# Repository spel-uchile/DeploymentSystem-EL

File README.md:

# DeploymentSystem-EL
Proyecto de curso EL. Diseño de sistema de despliegue

#### Parte eléctrica
 - Diseñar una nueva placa con un micro más pequeño y utilizando el espacio en los InterStage.
 - Revisar documentacion de Pinout de Stack (https://docs.google.com/spreadsheets/d/16q0HoTVAfZYG_5lE80G09ZOd-HxBMbC0y2KJIxqkWWU/edit#gid=0).
 - Instrucciones con comandos. 
 
#### Parte Mecánica
 - Revisar articulaciones en CAD (Carpeta general de CAD: https://drive.google.com/drive/u/0/folders/1X1Ea6DyqA-4cPEp2hvyv38Jz5EprBwpk).
   "NO MODIFICAR DIRECTAMENTE"
 - Leer CubesatRev 13 especificaciones de diseños (Tolerancias de diseños, dimensiones maximas de extrucción, estandar de dimensión). https://www.cubesat.org/resources.
 - Exportar las caras de los InterStage a DXF para el diseño del Board.
 - Crear articulaciones en los paneles.

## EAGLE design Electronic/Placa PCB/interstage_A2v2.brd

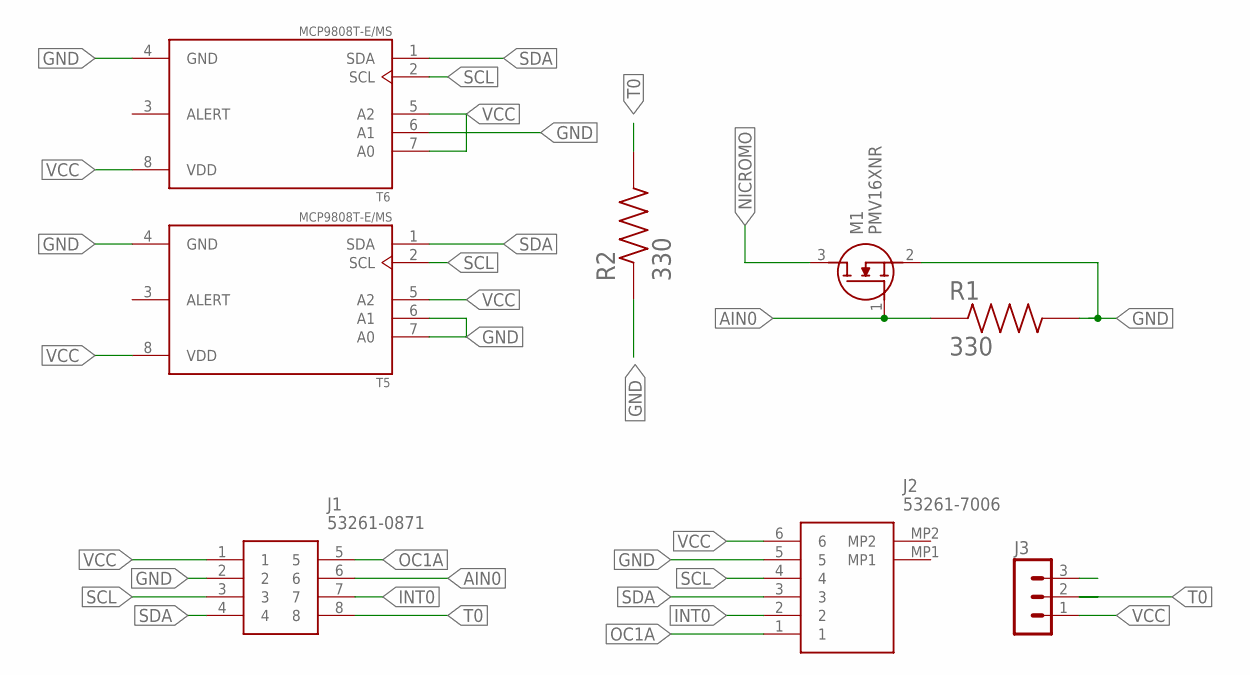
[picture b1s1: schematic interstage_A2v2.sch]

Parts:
J1: 53261-0871
J2: 53261-7006; 532617006
J3: MA03-1
M1: PMV16XNR; SOT95P230X110-3N
R1, R2: 330; RESC3216X70N
T5, T6: MCP9808T-E/MS; SOP65P490X110-8N

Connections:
AIN0: J1.6, M1.1 (G), R1.1
GND: J1.2, J2.5, M1.2 (S), R1.2, R2.1, T5.4 (GND), T5.6 (A1), T5.7 (A0), T6.4 (GND), T6.6 (A1)
INT0: J1.7, J2.2
NICROMO: M1.3 (D)
OC1A: J1.5, J2.1
SCL: J1.3, J2.4, T5.2 (SCL), T6.2 (SCL)
SDA: J1.4, J2.3, T5.1 (SDA), T6.1 (SDA)
T0: J1.8, J3.2, R2.2
VCC: J1.1, J2.6, J3.1, T5.5 (A2), T5.8 (VDD), T6.5 (A2), T6.7 (A0), T6.8 (VDD)

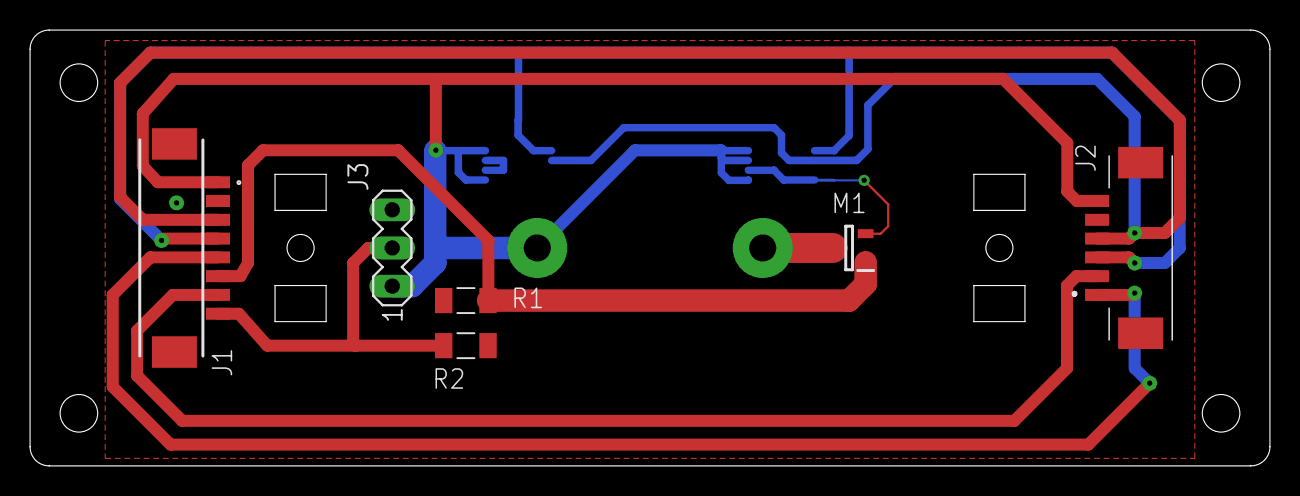
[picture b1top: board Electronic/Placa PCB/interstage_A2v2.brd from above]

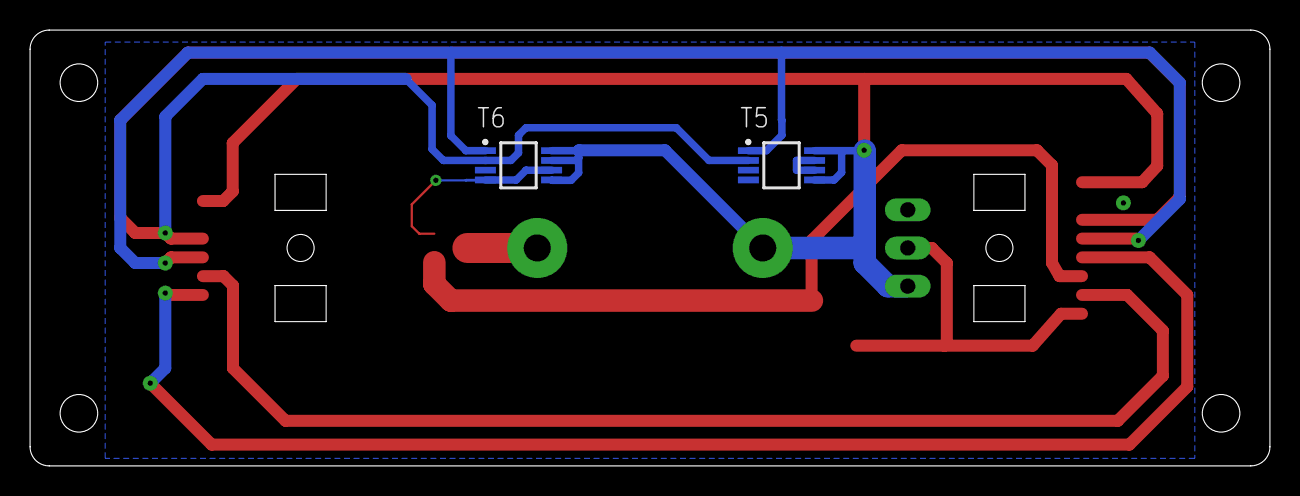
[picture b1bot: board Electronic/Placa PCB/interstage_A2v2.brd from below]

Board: 2 copper layers, 82.5 x 29.0 mm, 8 parts (2 on the bottom side), 8 nets.

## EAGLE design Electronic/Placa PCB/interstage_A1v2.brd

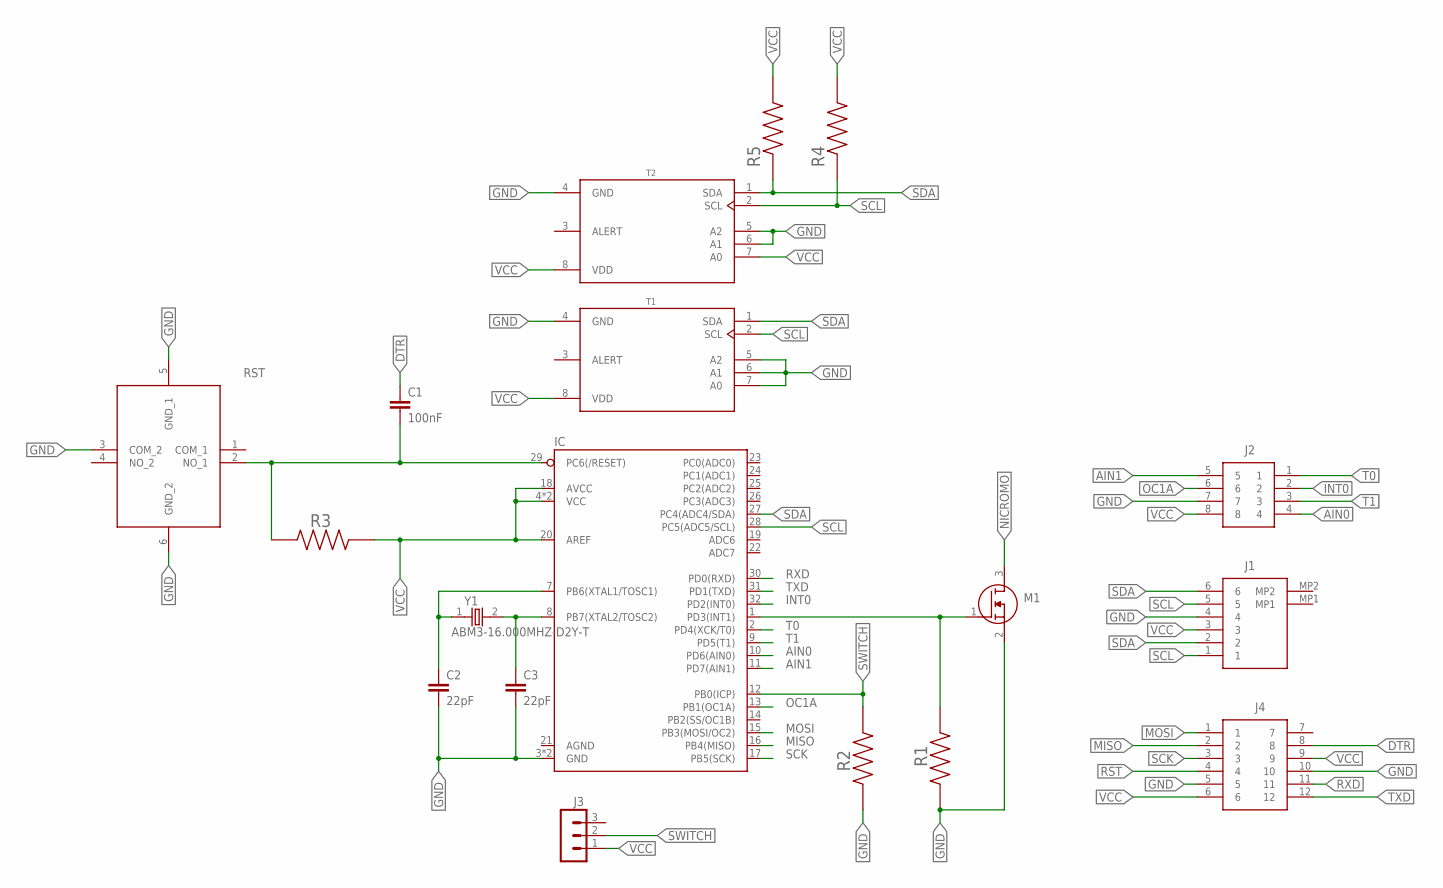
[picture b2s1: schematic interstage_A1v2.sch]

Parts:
C1: 100nF; C0805K
C2, C3: 22pF; C0603K
IC: ATMEGA328P_TQFP; TQFP32-08
J1: 53261-7006; 532617006
J2: 53261-0871
J3: MA03-1
J4: 53261-1271
M1: PMV16XNR; SOT95P230X110-3N
R1, R2: 330; RESC3216X70N
R3: 10k; RESC3216X70N
R4, R5: 4.7k; RESC3216X70N
RST: 431151015826
T1, T2: MCP9808T-E/MS; SOP65P490X110-8N
Y1: ABM3-16.000MHZ-D2Y-T; XTAL500X320X130N

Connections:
AIN0: IC.10 (PD6(AIN0)), J2.4
AIN1: IC.11 (PD7(AIN1)), J2.5
DTR: C1.1, J4.8
GND: C2.2, C3.2, IC.3 (GND), IC.5 (GND), J1.4, J2.7, J4.5, J4.10, M1.2 (S), R1.2, R2.1, RST.3 (COM_2), RST.5 (GND_1), RST.6 (GND_2), T1.4 (GND), T1.5 (A2), T1.6 (A1), T1.7 (A0), T2.4 (GND), T2.5 (A2), T2.6 (A1)
INT0: IC.32 (PD2(INT0)), J2.2
INT1: IC.1 (PD3(INT1)), M1.1 (G), R1.1
MISO: IC.16 (PB4(MISO)), J4.2
MOSI: IC.15 (PB3(MOSI/OC2)), J4.1
unnamed: C2.1, IC.7 (PB6(XTAL1/TOSC1)), Y1.1
unnamed: C3.1, IC.8 (PB7(XTAL2/TOSC2)), Y1.2
NICROMO: M1.3 (D)
OC1A: IC.13 (PB1(OC1A)), J2.6
RST: C1.2, IC.29 (PC6(/RESET)), J4.4, R3.1, RST.2 (NO_1)
RXD: IC.30 (PD0(RXD)), J4.11
SCK: IC.17 (PB5(SCK)), J4.3
SCL: IC.28 (PC5(ADC5/SCL)), J1.1, J1.5, R4.1, T1.2 (SCL), T2.2 (SCL)
SDA: IC.27 (PC4(ADC4/SDA)), J1.2, J1.6, R5.1, T1.1 (SDA), T2.1 (SDA)
SWITCH: IC.12 (PB0(ICP)), J3.2, R2.2
T0: IC.2 (PD4(XCK/T0)), J2.1
T1: IC.9 (PD5(T1)), J2.3
TXD: IC.31 (PD1(TXD)), J4.12
VCC: IC.4 (VCC), IC.6 (VCC), IC.18 (AVCC), IC.20 (AREF), J1.3, J2.8, J3.1, J4.6, J4.9, R3.2, R4.2, R5.2, T1.8 (VDD), T2.7 (A0), T2.8 (VDD)

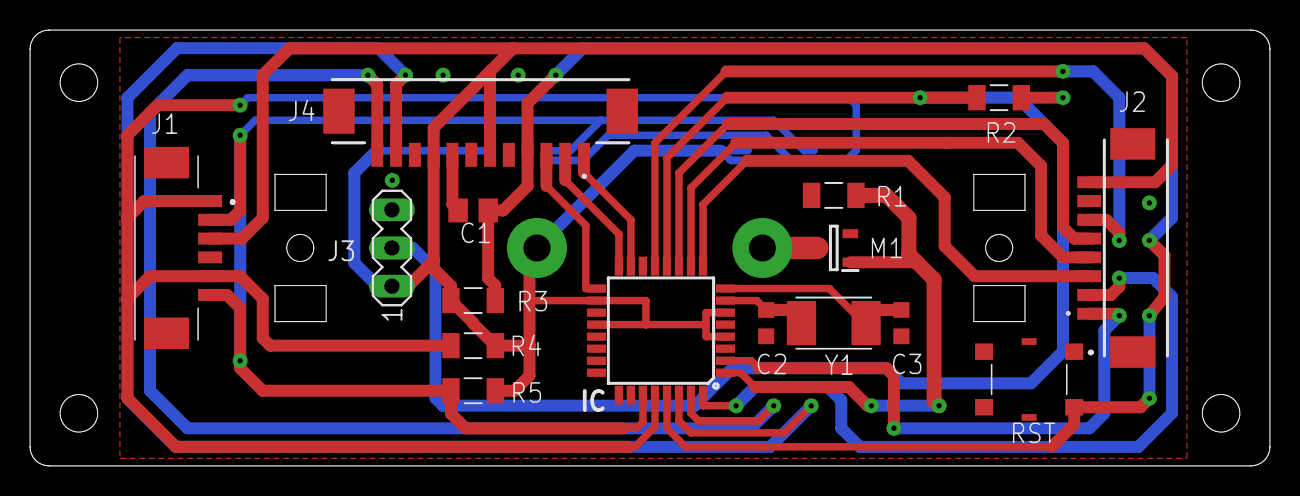
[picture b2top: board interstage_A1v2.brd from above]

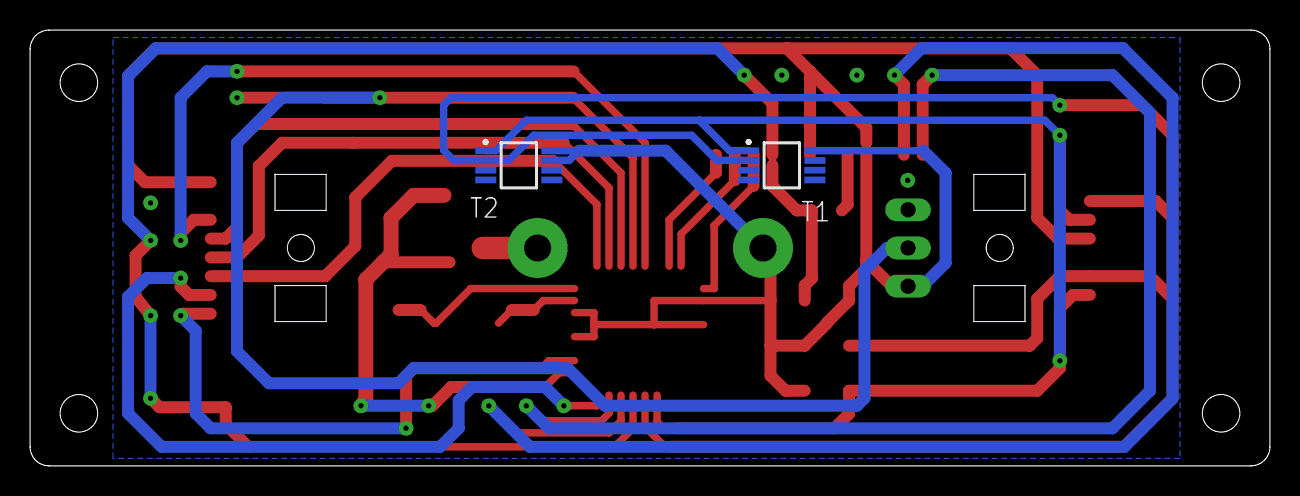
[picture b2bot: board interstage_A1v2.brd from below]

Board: 2 copper layers, 82.5 x 29.0 mm, 18 parts (2 on the bottom side), 21 nets.

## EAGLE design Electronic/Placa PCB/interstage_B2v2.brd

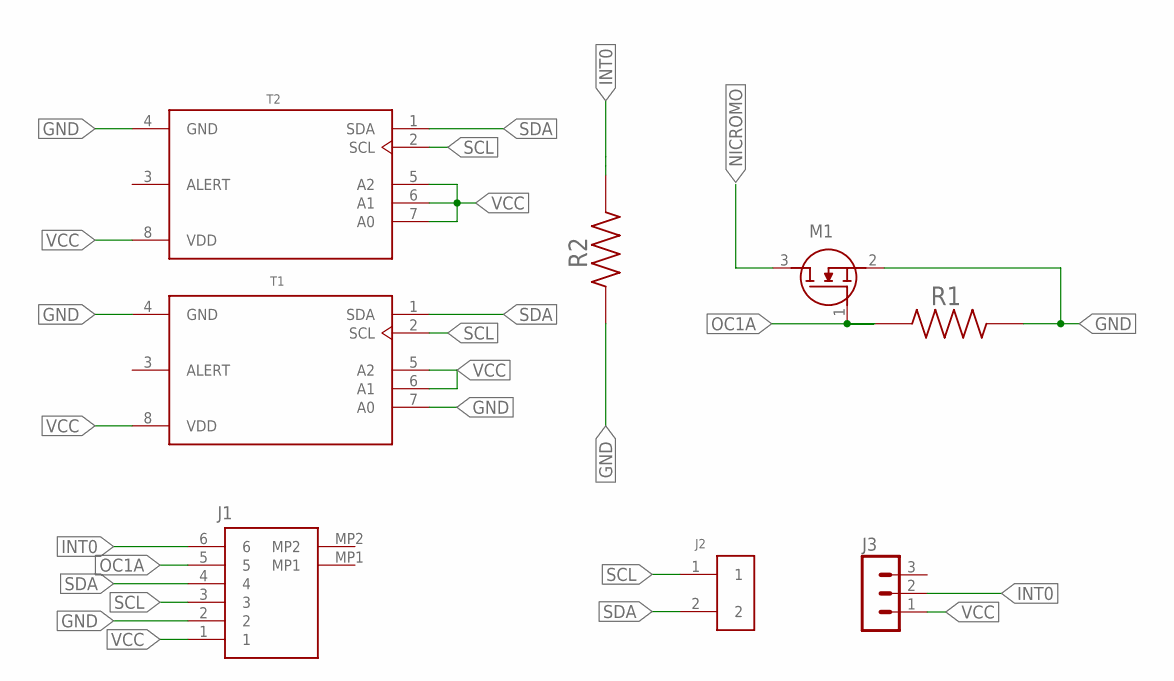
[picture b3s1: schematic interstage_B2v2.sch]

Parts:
J1: 53261-7006; 532617006
J2: 0532610271; MOLEX_0532610271
J3: MA03-1
M1: PMV16XNR; SOT95P230X110-3N
R1, R2: 330; RESC3216X70N
T1, T2: MCP9808T-E/MS; SOP65P490X110-8N

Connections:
GND: J1.2, M1.2 (S), R1.2, R2.1, T1.4 (GND), T1.7 (A0), T2.4 (GND)
INT0: J1.6, J3.2, R2.2
NICROMO: M1.3 (D)
OC1A: J1.5, M1.1 (G), R1.1
SCL: J1.3, J2.1, T1.2 (SCL), T2.2 (SCL)
SDA: J1.4, J2.2, T1.1 (SDA), T2.1 (SDA)
VCC: J1.1, J3.1, T1.5 (A2), T1.6 (A1), T1.8 (VDD), T2.5 (A2), T2.6 (A1), T2.7 (A0), T2.8 (VDD)

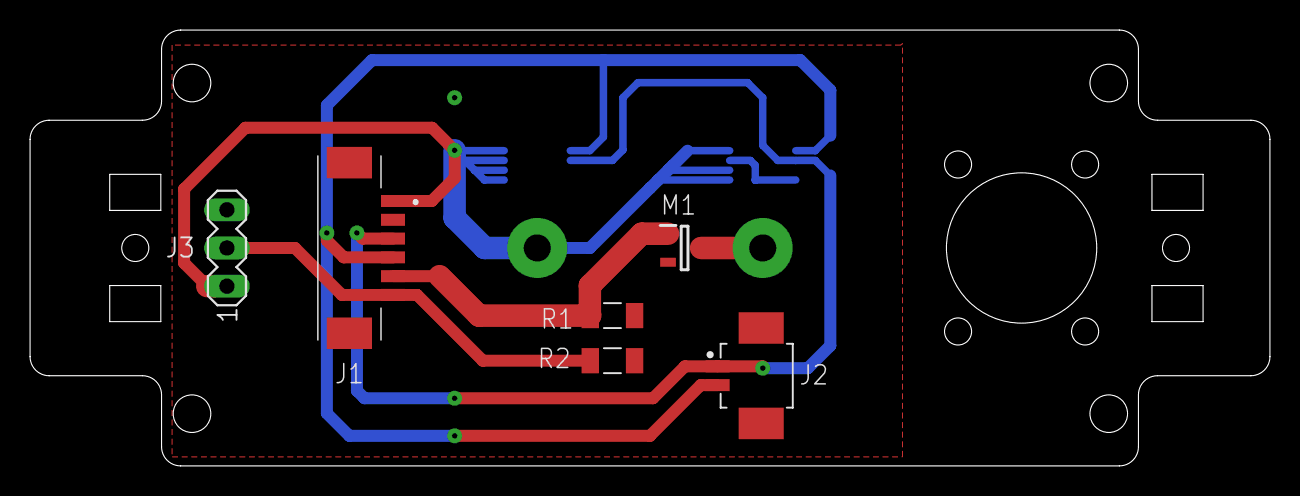
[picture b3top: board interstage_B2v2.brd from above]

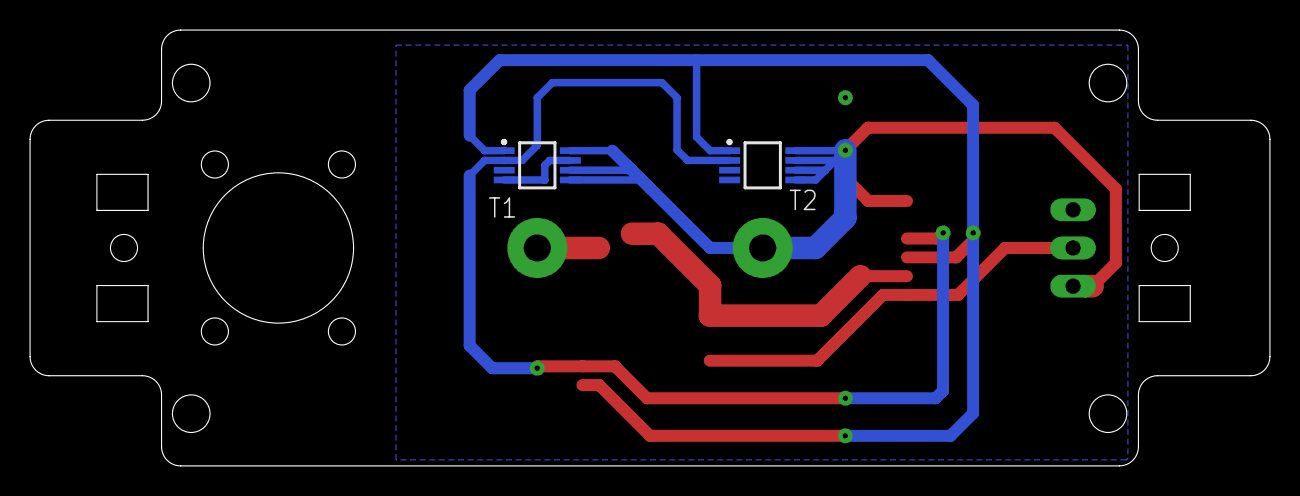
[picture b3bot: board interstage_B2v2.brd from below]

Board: 2 copper layers, 82.5 x 29.0 mm, 8 parts (2 on the bottom side), 6 nets.

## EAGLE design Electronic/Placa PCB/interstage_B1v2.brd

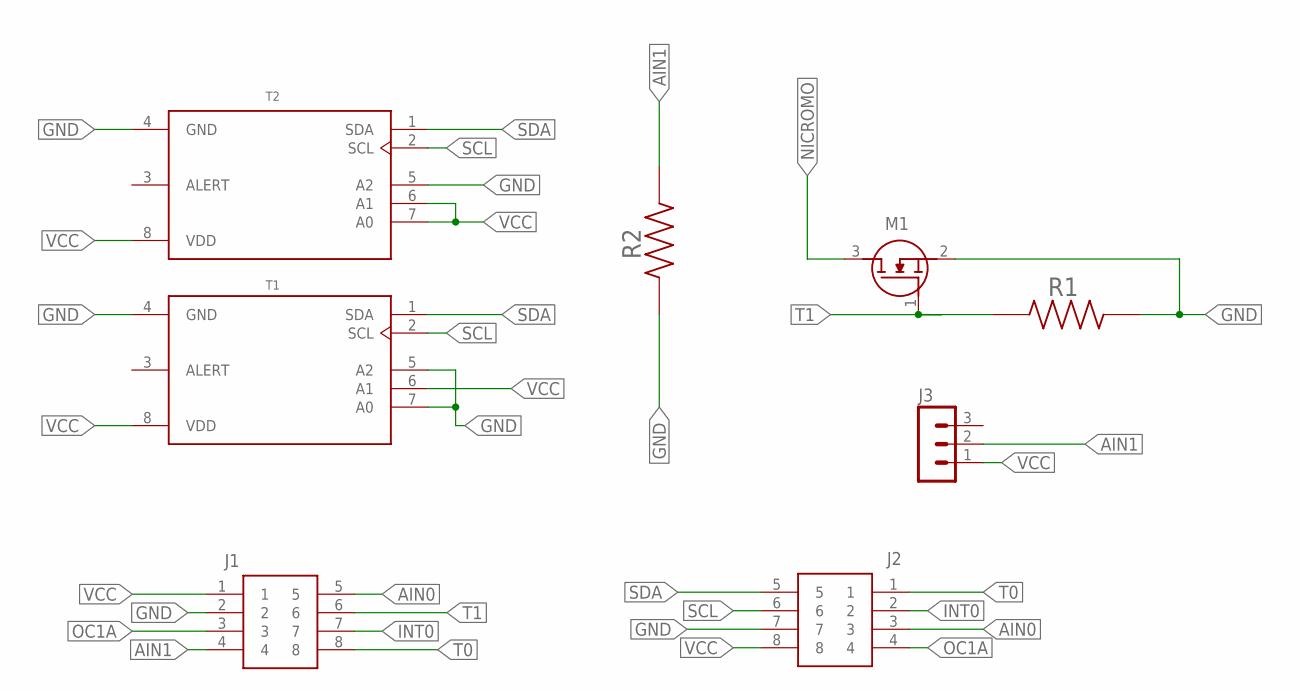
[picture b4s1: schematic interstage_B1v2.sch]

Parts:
J1, J2: 53261-0871
J3: MA03-1
M1: PMV16XNR; SOT95P230X110-3N
R1, R2: 330; RESC3216X70N
T1, T2: MCP9808T-E/MS; SOP65P490X110-8N

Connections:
AIN0: J1.5, J2.3
AIN1: J1.4, J3.2, R2.2
GND: J1.2, J2.7, M1.2 (S), R1.2, R2.1, T1.4 (GND), T1.5 (A2), T1.7 (A0), T2.4 (GND), T2.5 (A2)
INT0: J1.7, J2.2
NICROMO: M1.3 (D)
OC1A: J1.3, J2.4
SCL: J2.6, T1.2 (SCL), T2.2 (SCL)
SDA: J2.5, T1.1 (SDA), T2.1 (SDA)
T0: J1.8, J2.1
T1: J1.6, M1.1 (G), R1.1
VCC: J1.1, J2.8, J3.1, T1.6 (A1), T1.8 (VDD), T2.6 (A1), T2.7 (A0), T2.8 (VDD)

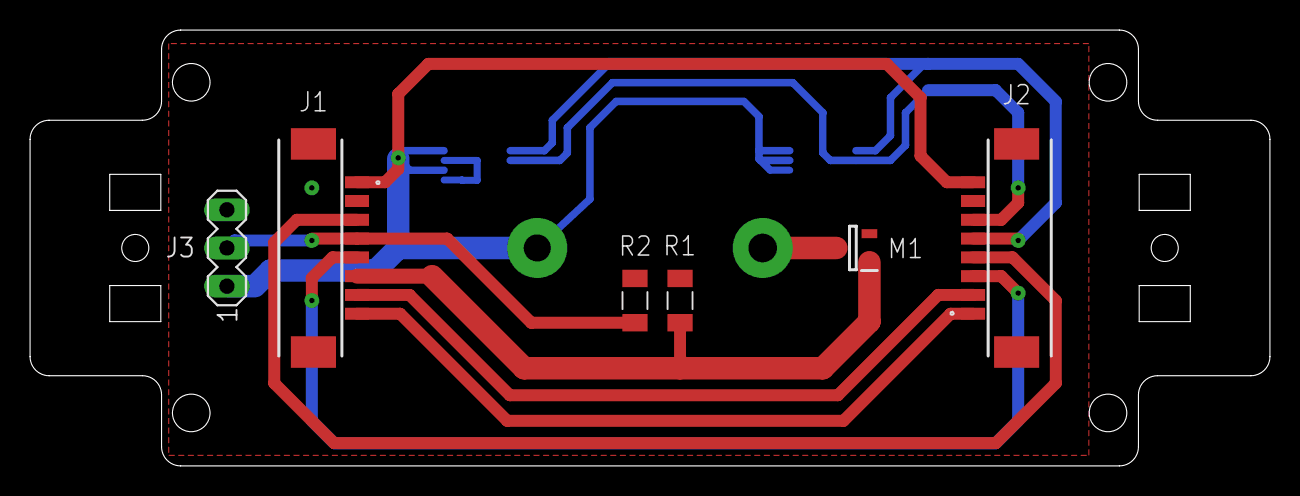
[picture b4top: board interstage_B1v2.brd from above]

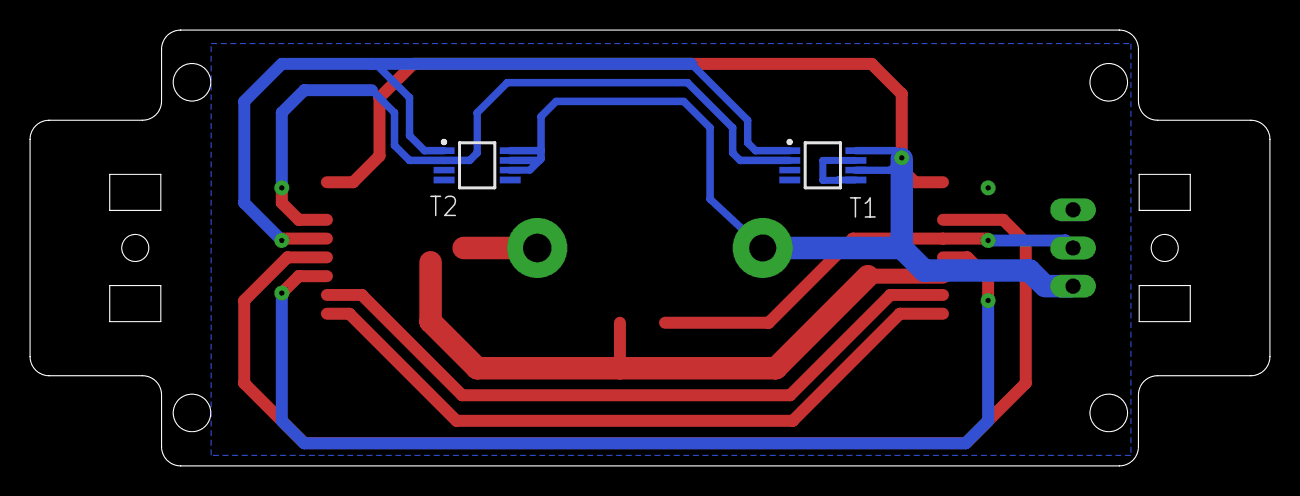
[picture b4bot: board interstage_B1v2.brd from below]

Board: 2 copper layers, 82.5 x 29.0 mm, 8 parts (2 on the bottom side), 10 nets.

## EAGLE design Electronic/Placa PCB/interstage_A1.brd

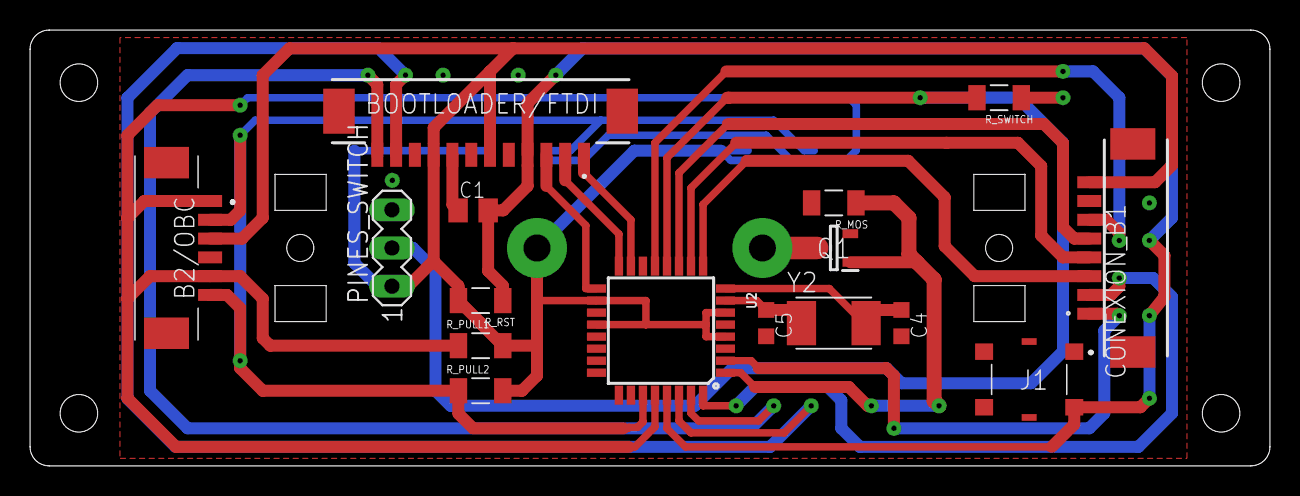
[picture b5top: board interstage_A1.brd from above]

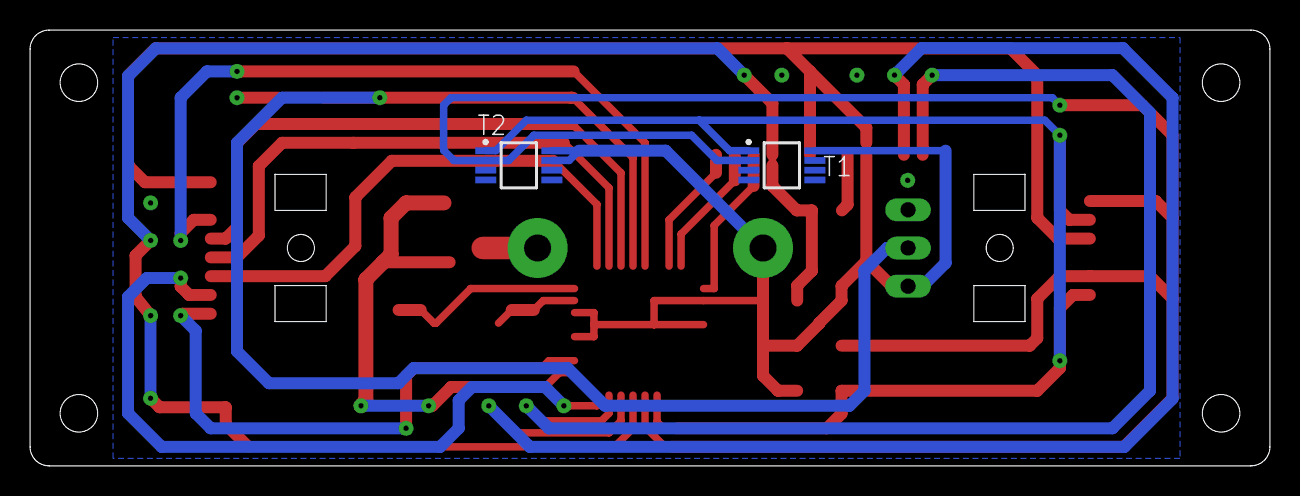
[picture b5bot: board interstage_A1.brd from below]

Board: 2 copper layers, 82.5 x 29.0 mm, 18 parts (2 on the bottom side), 21 nets.

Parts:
B2/OBC: 53261-7006; 532617006
BOOTLOADER/FTDI: 53261-1271
C1: 100nF; C0805K
C4, C5: 22pF; C0603K
CONEXION_B1: 53261-0871
J1: 431151015826
PINES_SWITCH: MA03-1
Q1: PMV16XNR; SOT95P230X110-3N
R_MOS: ERA-8AEB331V; RESC3216X70N
R_PULL1, R_PULL2: ERA-8AEB472V; RESC3216X70N
R_RST: ERA-8AEB103V; RESC3216X70N
R_SWITCH: ERA-8AEB331V; RESC3216X70N
T1, T2: MCP9808T-E/MS; SOP65P490X110-8N
U2: ATMEGA328P_TQFP; TQFP32-08
Y2: ABM3-16.000MHZ-D2Y-T; XTAL500X320X130N

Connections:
AIN0: CONEXION_B1.4, U2.10
AIN1: CONEXION_B1.5, U2.11
DTR: BOOTLOADER/FTDI.8, C1.1
GND: B2/OBC.4, BOOTLOADER/FTDI.5, BOOTLOADER/FTDI.10, C4.2, C5.2, CONEXION_B1.7, J1.3, J1.5, J1.6, Q1.2, R_MOS.2, R_SWITCH.1, T1.4, T1.5, T1.6, T1.7, T2.4, T2.5, T2.6, U2.3, U2.5
INT0: CONEXION_B1.2, U2.32
INT1: Q1.1, R_MOS.1, U2.1
MISO: BOOTLOADER/FTDI.2, U2.16
MOSI: BOOTLOADER/FTDI.1, U2.15
unnamed: C5.1, U2.7, Y2.1
unnamed: C4.1, U2.8, Y2.2
OC1A: CONEXION_B1.6, U2.13
RST: BOOTLOADER/FTDI.4, C1.2, J1.2, R_RST.1, U2.29
RXD: BOOTLOADER/FTDI.11, U2.30
SCK: BOOTLOADER/FTDI.3, U2.17
SCL: B2/OBC.1, B2/OBC.5, R_PULL1.1, T1.2, T2.2, U2.28
SDA: B2/OBC.2, B2/OBC.6, R_PULL2.1, T1.1, T2.1, U2.27
SWITCH: PINES_SWITCH.2, R_SWITCH.2, U2.12
T0: CONEXION_B1.1, U2.2
T1: CONEXION_B1.3, U2.9
TXD: BOOTLOADER/FTDI.12, U2.31
VCC: B2/OBC.3, BOOTLOADER/FTDI.6, BOOTLOADER/FTDI.9, CONEXION_B1.8, PINES_SWITCH.1, R_PULL1.2, R_PULL2.2, R_RST.2, T1.8, T2.7, T2.8, U2.4, U2.6, U2.18, U2.20

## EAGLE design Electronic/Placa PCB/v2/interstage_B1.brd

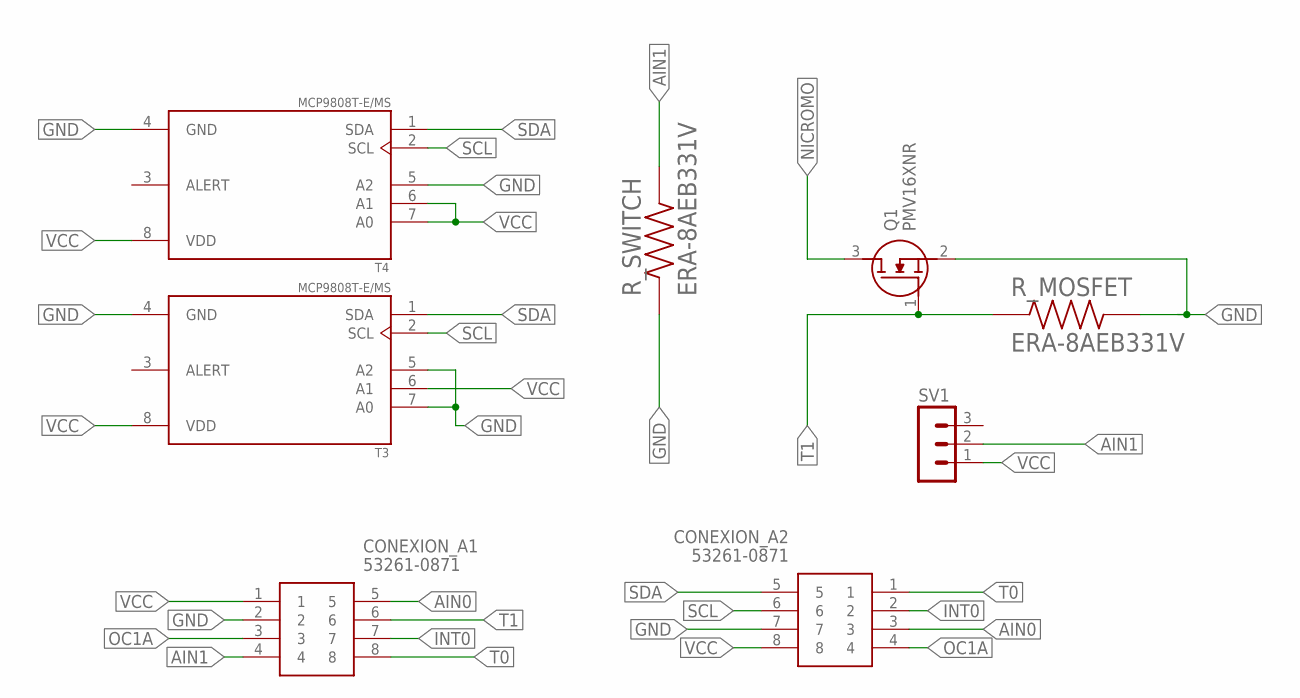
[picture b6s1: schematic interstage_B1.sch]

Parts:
CONEXION_A1, CONEXION_A2: 53261-0871
Q1: PMV16XNR; SOT95P230X110-3N
R_MOSFET: ERA-8AEB331V; RESC3216X70N
R_SWITCH: ERA-8AEB331V; RESC3216X70N
SV1: MA03-1
T3, T4: MCP9808T-E/MS; SOP65P490X110-8N

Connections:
AIN0: CONEXION_A1.5, CONEXION_A2.3
AIN1: CONEXION_A1.4, R_SWITCH.2, SV1.2
GND: CONEXION_A1.2, CONEXION_A2.7, Q1.2 (S), R_MOSFET.2, R_SWITCH.1, T3.4 (GND), T3.5 (A2), T3.7 (A0), T4.4 (GND), T4.5 (A2)
INT0: CONEXION_A1.7, CONEXION_A2.2
NICROMO: Q1.3 (D)
OC1A: CONEXION_A1.3, CONEXION_A2.4
SCL: CONEXION_A2.6, T3.2 (SCL), T4.2 (SCL)
SDA: CONEXION_A2.5, T3.1 (SDA), T4.1 (SDA)
T0: CONEXION_A1.8, CONEXION_A2.1
T1: CONEXION_A1.6, Q1.1 (G), R_MOSFET.1
VCC: CONEXION_A1.1, CONEXION_A2.8, SV1.1, T3.6 (A1), T3.8 (VDD), T4.6 (A1), T4.7 (A0), T4.8 (VDD)

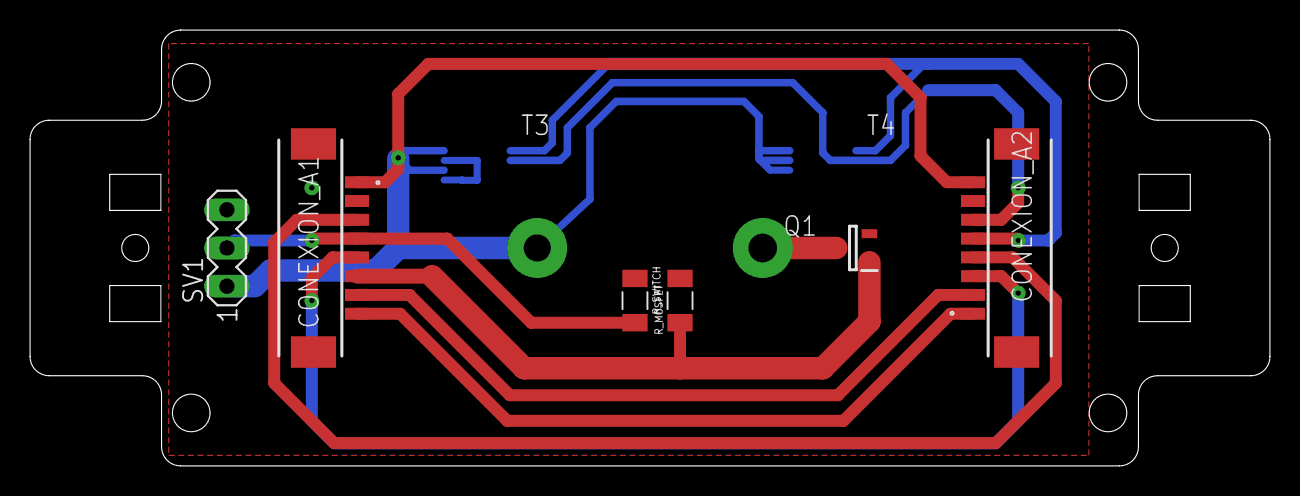
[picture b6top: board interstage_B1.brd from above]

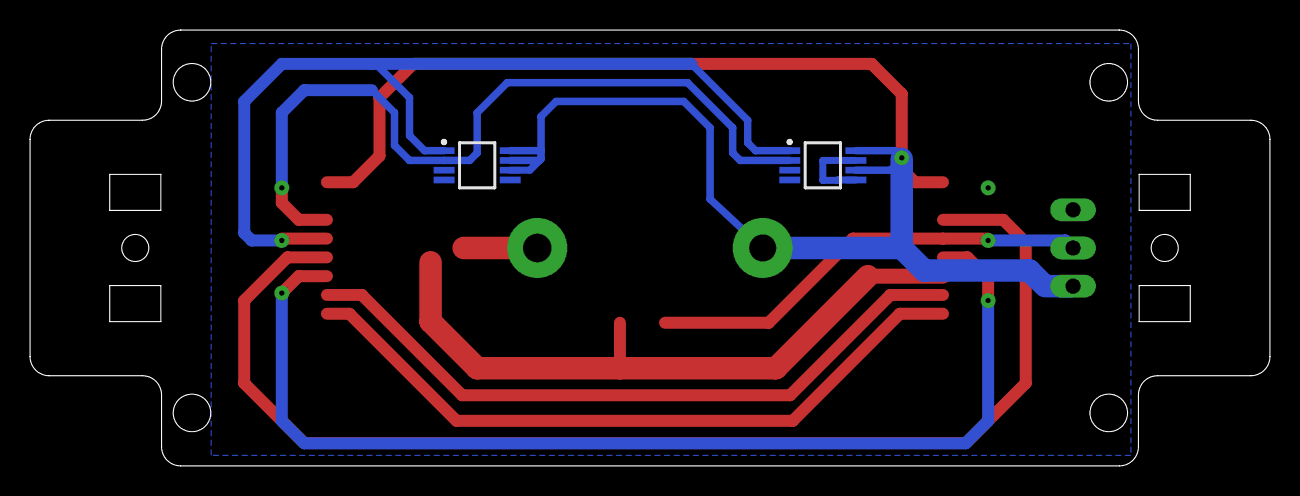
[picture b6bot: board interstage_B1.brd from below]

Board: 2 copper layers, 82.5 x 29.0 mm, 8 parts (2 on the bottom side), 10 nets.

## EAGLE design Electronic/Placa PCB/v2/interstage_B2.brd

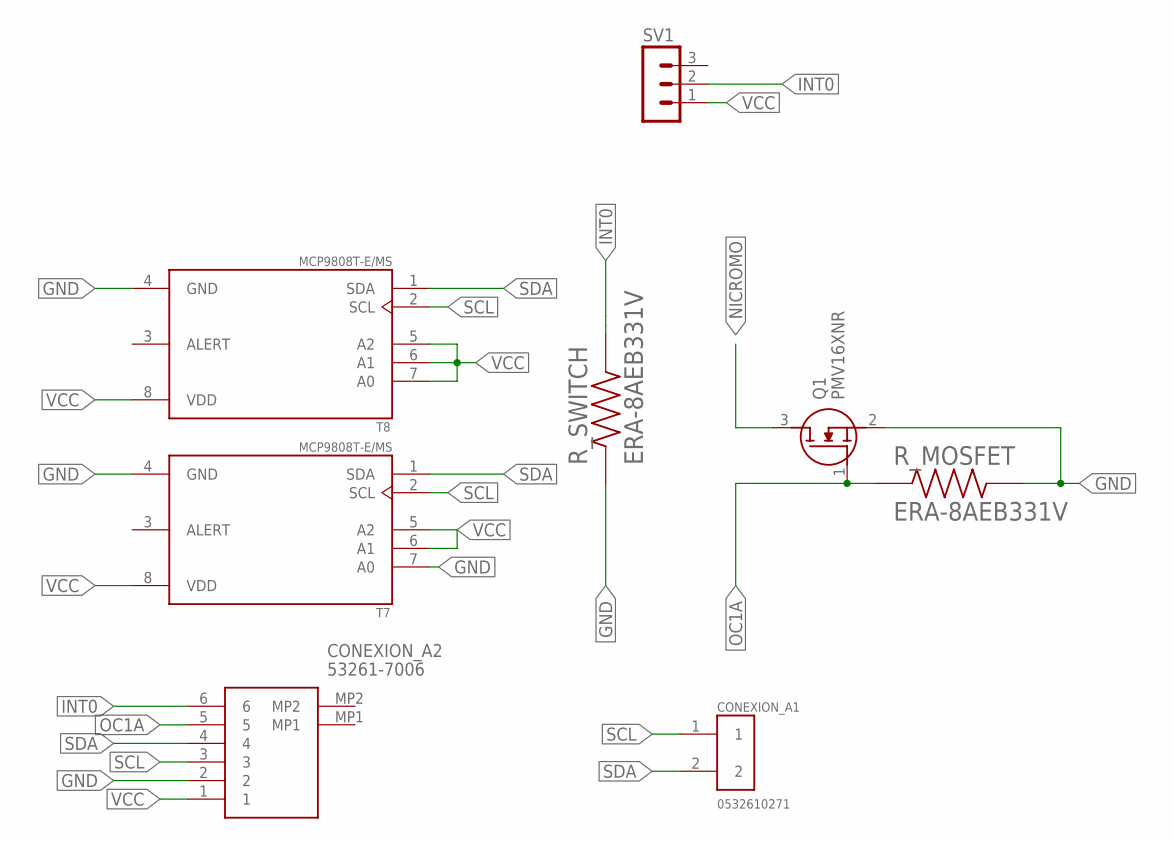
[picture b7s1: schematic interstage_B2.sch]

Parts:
CONEXION_A1: 0532610271; MOLEX_0532610271
CONEXION_A2: 53261-7006; 532617006
Q1: PMV16XNR; SOT95P230X110-3N
R_MOSFET: ERA-8AEB331V; RESC3216X70N
R_SWITCH: ERA-8AEB331V; RESC3216X70N
SV1: MA03-1
T7, T8: MCP9808T-E/MS; SOP65P490X110-8N

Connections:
GND: CONEXION_A2.2, Q1.2 (S), R_MOSFET.2, R_SWITCH.1, T7.4 (GND), T7.7 (A0), T8.4 (GND)
INT0: CONEXION_A2.6, R_SWITCH.2, SV1.2
NICROMO: Q1.3 (D)
OC1A: CONEXION_A2.5, Q1.1 (G), R_MOSFET.1
SCL: CONEXION_A1.1, CONEXION_A2.3, T7.2 (SCL), T8.2 (SCL)
SDA: CONEXION_A1.2, CONEXION_A2.4, T7.1 (SDA), T8.1 (SDA)
VCC: CONEXION_A2.1, SV1.1, T7.5 (A2), T7.6 (A1), T7.8 (VDD), T8.5 (A2), T8.6 (A1), T8.7 (A0), T8.8 (VDD)

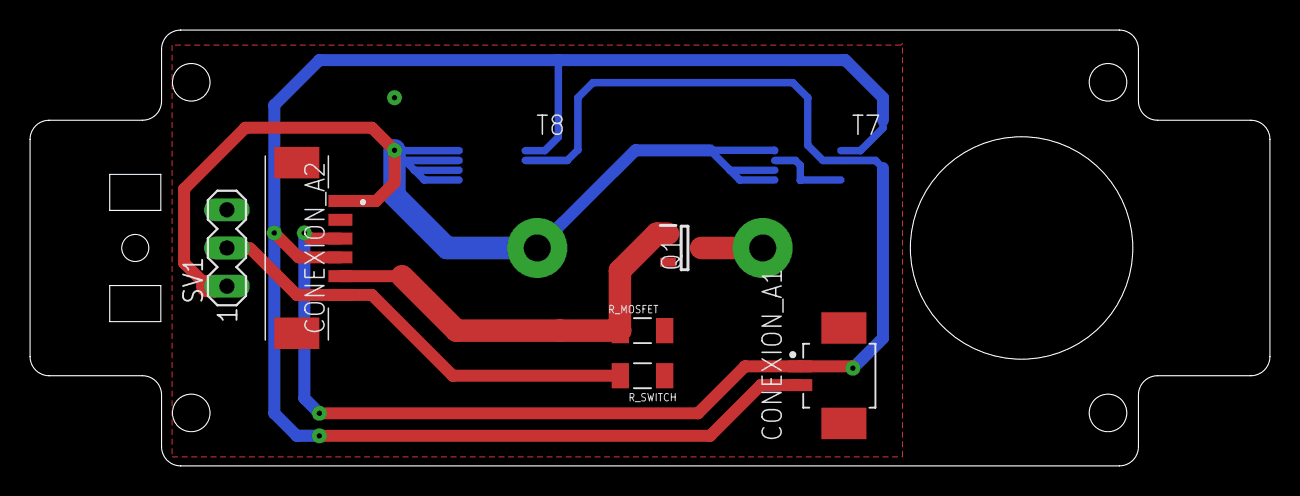
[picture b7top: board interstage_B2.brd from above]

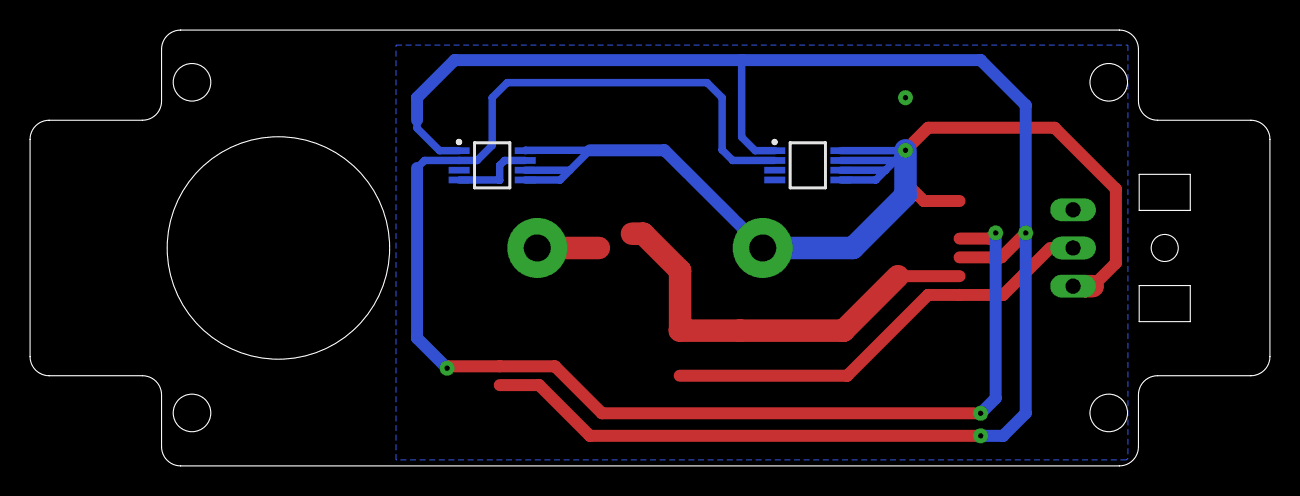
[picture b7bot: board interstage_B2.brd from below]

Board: 2 copper layers, 82.5 x 29.0 mm, 8 parts (2 on the bottom side), 6 nets.

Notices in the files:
parts and their libraries:
SparkFun-IC-Microcontroller: Licensing: Creative Commons ShareAlike 4.0 International - https://creativecommons.org/licenses/by-sa/4.0
